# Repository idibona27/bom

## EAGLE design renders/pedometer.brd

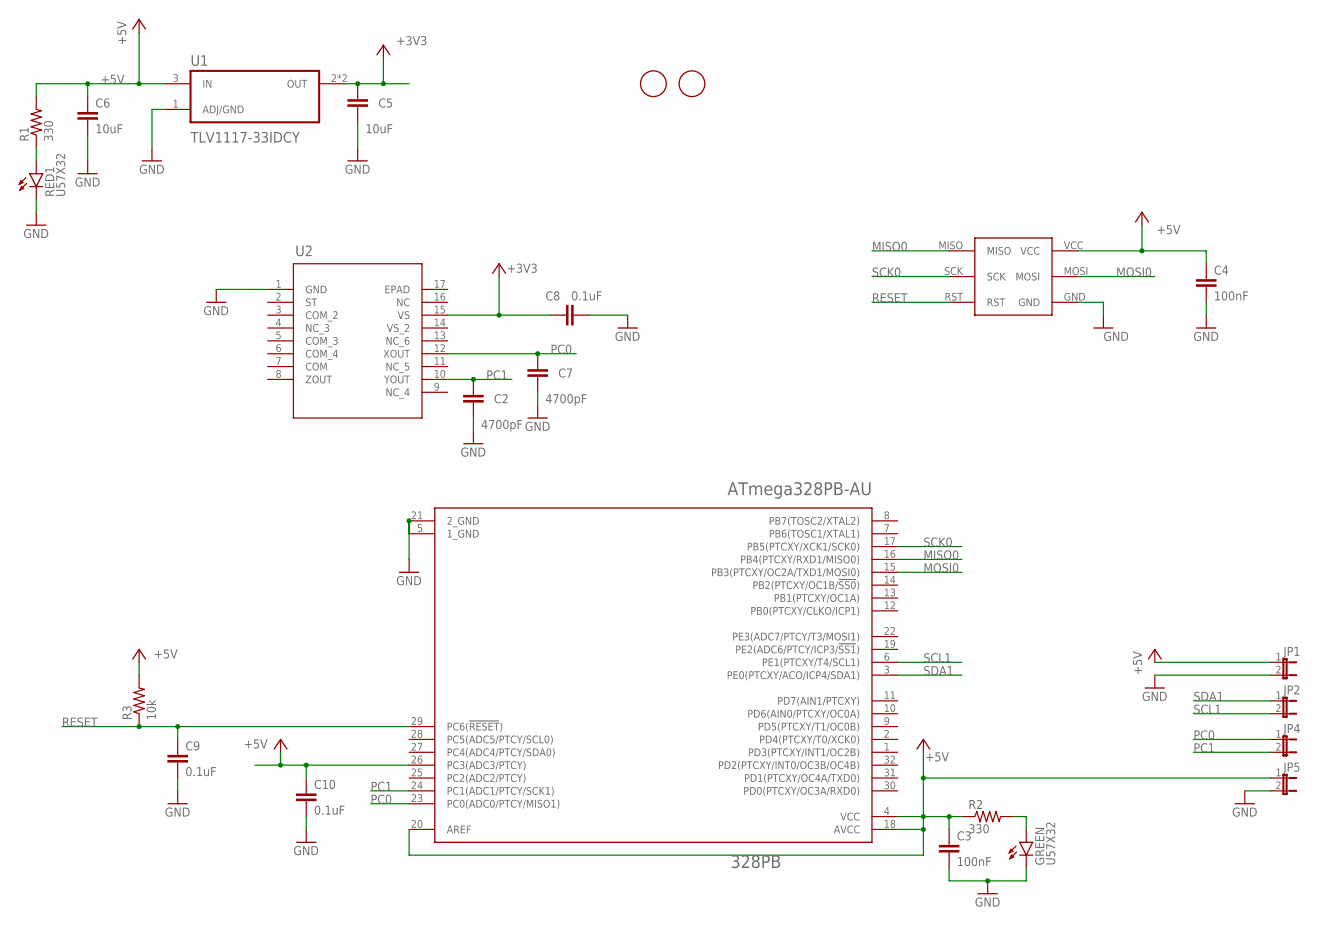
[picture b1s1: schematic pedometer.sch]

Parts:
328PB: MICROCHIP_ATMEGA328PB-AUMICROCHIP_ATMEGA328PB-AU_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; MICROCHIP_ATMEGA328PB-AU_0
C2, C7: 4700pF; C0805K
C3, C4: 100nF; C0805K
C5, C6: 10uF; C0805K
C8, C9, C10: 0.1uF; C0805K
GREEN: U57X32
JP1, JP2, JP4, JP5: JP1E; JP1
R1, R2: 330; R0805
R3: 10k; R0805
RED1: U57X32
U1: TLV1117-33IDCY; SOT230P700X180-4N
U2: ADXL327BCPZ-RL7CP_16_5A_ADI-M; CP_16_5A_ADI-M
U$1: AVR-ISP
U$2, U$3: FIDUCIAL; FIDUCIAL_1MM

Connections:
+3V3: C5.2, C8.2, U1.2 (OUT), U1.4 (OUT), U2.15 (VS)
+5V: 328PB.4 (VCC), 328PB.18 (AVCC), 328PB.20 (AREF), 328PB.26 (PC3(ADC3/PTCY)), C3.2, C4.2, C6.2, C10.2, JP1.1, JP5.1, R1.2, R2.1, R3.2, U1.3 (IN), U$1.VCC
GND: 328PB.5 (1_GND), 328PB.21 (2_GND), C2.1, C3.1, C4.1, C5.1, C6.1, C7.1, C8.1, C9.1, C10.1, GREEN.K (C), JP1.2, JP5.2, RED1.K (C), U1.1 (ADJ/GND), U2.1 (GND), U$1.GND
MISO0: 328PB.16 (PB4(PTCXY/RXD1/MISO0)), U$1.MISO
MOSI0: 328PB.15 (PB3(PTCXY/OC2A/TXD1/MOSI0)), U$1.MOSI
unnamed: GREEN.A, R2.2
unnamed: R1.1, RED1.A
PC0: 328PB.23 (PC0(ADC0/PTCY/MISO1)), C7.2, JP4.1, U2.12 (XOUT)
PC1: 328PB.24 (PC1(ADC1/PTCY/SCK1)), C2.2, JP4.2, U2.10 (YOUT)
RESET: 328PB.29 (PC6(!RESET!)), C9.2, R3.1, U$1.RST
SCK0: 328PB.17 (PB5(PTCXY/XCK1/SCK0)), U$1.SCK
SCL1: 328PB.6 (PE1(PTCXY/T4/SCL1)), JP2.2
SDA1: 328PB.3 (PE0(PTCXY/ACO/ICP4/SDA1)), JP2.1

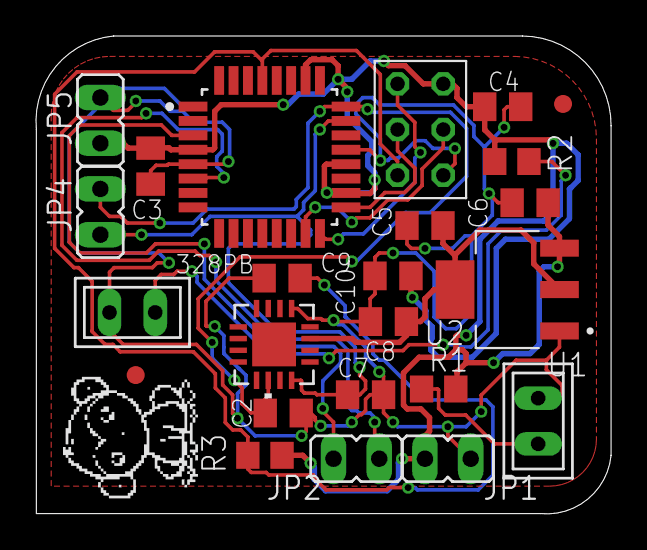
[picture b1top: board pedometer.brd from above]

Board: 2 copper layers, 31.9 x 26.5 mm, 24 parts (0 on the bottom side), 13 nets.

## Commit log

2020-10-11 Create BOM Submission
2020-10-13 Create DRC and Cam
2020-10-13 Create Output Files
2020-10-13 Create whenTo_Step
2020-10-13 Create bill of materials
2020-10-17 Create 1017whentostep
2020-10-17 Update whenTo_Step
2020-11-11 Add files via upload
    This is most recent schematic
2020-12-08 Create video_demo
2020-12-08 Create demos
2021-03-07 Create files
2021-03-07 Create file
2021-03-07 Create reports
2021-03-07 Rename pedometer_assembly.csv to BOM Submission/pedometer_assembly.csv

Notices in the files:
parts and their libraries:
COPYRIGHT: Copyright (C) 2018 Accelerated Designs. All rights reserved
